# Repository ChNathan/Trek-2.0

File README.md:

# Trek-2.0
Project report and files for Oslo Met EPS project. We built a gait tracker for real time gait asymmetry over varying windows.

Included in this Repo Are:
- Trek EPS Report ( Which is covered in additional detail via this presentation https://docs.google.com/presentation/d/1eJzCRBbl3npr1pbE6kb9zn8NsA4ln3SlZraTO1EqVzs/edit?usp=sharing )
  - This report includes the project's purpose, progress, and future recommendations. We believe this project could be piloted in research studies with an additional project iteration.
- Firmware Code for Left and Right device, with and without SD Card
- User Interface Code
- Short user manual on setting up the device
- Autodesk Invetor CAD File for Case
- KiCad PCB Schematics, BOM, and additional design files

For any questions, comments, or concerns, please don't hestitate to contact us.
- Group 1, EPS Fall 2025

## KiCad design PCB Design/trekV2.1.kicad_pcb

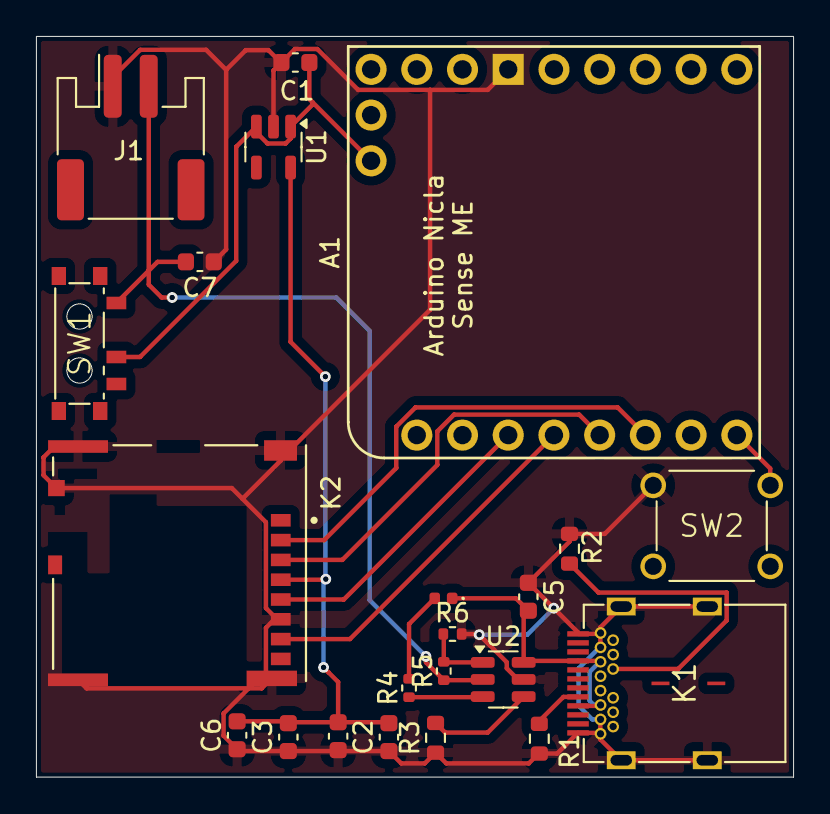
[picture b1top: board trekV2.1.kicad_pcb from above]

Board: 2 copper layers, 42.1 x 41.1 mm, 22 parts (0 on the bottom side), 16 nets.

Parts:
A1: Arduino_Nicla_Sense_ME_Socket; Arduino_Nicla_Voice_Socket
C1, C2, C5, C6: 2u2; C_0603_1608Metric
C3, C4: 100n; C_0603_1608Metric
C7: 4.7uF; C_0603_1608Metric
D1: red; LED_0402_1005Metric
J1: JST_02; JST_PH_S2B-PH-SM4-TB_1x02-1MP_P2.00mm_Horizontal
K1: 632723100011 USBC; CONN_WURTH_632723100011
K2: 503398-1892; MOLEX_503398-1892
R1, R2: 5k1; R_0603_1608Metric
R3: 1.33K; R_0603_1608Metric
R4: 2k2; R_0402_1005Metric
R5, R6: 10K; R_0402_1005Metric
SW1: Slide_Switch_SPDT_P3mm_10x5x10mm; SW_WURTH_450404015514
SW2: Push_Button; SW_KARSON_970-001-03-00
U1: SE5218; SOT-23-5
U2: BQ21040DBV; SOT-23-6

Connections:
3V3: C2.2, C3.2, C4.2, C6.2, K2.4 (VDD), U1.5 (VOUT)
CS_L: A1.D6 (D6_CS), K2.2 (CD/DAT3^2)
GND: A1.GND, C1.1, C2.1, C3.1, C4.1, C5.1, C6.1, C7.1, J1.1, K1.A1 (GND), K1.A12 (GND1), K1.B1 (GND2), K1.B12 (GND3), K1.GND, K1.GND1, K1.S1, K1.S2, K1.S3, K1.S4, K2.6 (VSS), K2.9 (VSS), K2.P1 (SHIELD), K2.P2 (SHIELD), K2.P3 (SHIELD), K2.P4 (SHIELD), R1.2, R2.2, R3.1, R6.2, SW2.2, U1.2 (GND), U2.5 (GND)
MISO_L: A1.D7 (D7_MISO), K2.7 (DAT0)
MOSI_L: A1.D8 (D8_MOSI), K2.3 (CMD)
unnamed: A1.D5, SW2.1
unnamed: D1.2 (K), R4.2
unnamed: K1.A5 (CC), R1.1
unnamed: K1.B5 (VCONN), R2.1
unnamed: R3.2, U2.4 (ISET)
unnamed: R5.2, R6.1, U2.1 (TS)
unnamed: R4.1, U2.3 (~CHG)
SCLK_L: A1.D9 (D9_SCK), K2.5 (CLK)
VBATRAW: C7.2, J1.2, R5.1, SW1.1, U2.2 (OUT)
VBATSYS: A1.VBAT, C1.2, SW1.2, U1.1 (VIN), U1.3 (EN)
VUSB: C5.2, D1.1 (A), K1.A4 (VBUS), K1.A9 (VBUS1), K1.B4 (VBUS2), K1.B9 (VBUS3), U2.6 (VIN)

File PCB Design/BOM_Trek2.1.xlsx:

Designators | Qty | Value | Description | Manufacturer | MPN | Package | Notes / DNP
U2 | 1.0 | BQ21040 | Li-ion 1-cell linear charger, SOT-23-6 | Texas Instruments | BQ21040DBVT | SOT-23-6 | TS mid-bias: R5/R6 10 k
U1 | 1.0 | 3.3 V, 600 mA | LDO Regulator, 3.3 V fixed, SOT-23-5 | SEASemi (or alt.) | SE5218-33 (alt: AP2112K-3.3) | SOT-23-5 | Input/Output caps 2.2 µF
K1 | 1.0 | USB-C Receptacle | 24-pin right-angle receptacle, mixed TH/SMD | Würth Elektronik | 6.32723100011E11 | Custom (mixed) | TH shell lugs to GND; hand-solder if no THT assembly
K2 | 1.0 | microSD Socket | Hinged microSD holder | Molex | 503398-1892 | Molex microSD | Place decouplers close
J1 | 1.0 | 2-pin, 2.0 mm | JST-PH battery header, side-entry, SMD | JST | BM02B-PH-SM4-TB(LF)(SN) | SMD | Battery connector
SW1 | 1.0 | SPDT | Slide switch, 3 mm pitch, ~10×5×10 mm | Generic / C&K | (e.g.) JS102011SAQN | TH | Battery isolate selector
SW2 | 1.0 | Momentary | THT pushbutton, 9.5 mm actuator | Karson | 970-001-03-00 | TH | Hand-solder if no THT assembly
D1 | 1.0 | Red LED | Red indicator LED | Any | 0402 red (e.g. LTST-C190KRKT) | 402.0 | Series R4 = 2.2 k to VUSB
R1, R2 | 2.0 | 5.1 k | USB-C CC pull-downs (to GND) | Any | 0.01 | 402.0 | For Sink-only
R3 | 1.0 | 1.33 k | BQ21040 ISET (charge current set) | Any | 0.01 | 402.0 | Sets I_CHG (~1 A per TI table)
R4 | 1.0 | 2.2 k | LED current-limit (D1) | Any | 0.01 | 402.0 | Red LED to VUSB
R5, R6 | 2.0 | 10 k | TS bias divider (midpoint ≈ VBAT/2) | Any | 0.01 | 402.0 | For thermistor bypass mode
C1 | 1.0 | 2.2 µF / 10 V | VIN (VUSB) input cap (charger) | Any | X5R/X7R | 603.0 | Close to U2 VIN
C7 | 1.0 | 4.7 µF / 6.3–10 V | VBAT output/rail cap (charger) | Any | X5R/X7R | 603.0 | Close to U2 OUT/VBAT
C2 | 1.0 | 2.2 µF / 10 V | LDO output (3V3) | Any | X5R/X7R | 603.0 | As per U1 datasheet
C5 | 1.0 | 2.2 µF / 10 V | LDO input (VCC/VBATSYS) | Any | X5R/X7R | 603.0 | As per U1 datasheet
C3, C4, C6 | 3.0 | 0.1 µF | Decouplers (microSD / local) | Any | X7R | 402.0 | Place close to K2 pins
FIDs (Top) | 3.0 | — | Global fiducials, 0.5 mm Cu, 1.5 mm mask | — | — | SMD pad | No paste; no net
A1 | 1.0 | Arduino Nicla | Castellated socket/footprint only | Arduino | Nicla Sense ME | Castellated | DNP (do not assemble)

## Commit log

2026-01-06 Initialize project folders with placeholders
2026-01-09 Jeya Codes
2026-01-09 Update README with project details and resources
    Added detailed project report and included links to resources.
2026-01-09 Thomas Codes
2026-01-14 Fix typo in README and add image
2026-01-14 Replace old image with a new one in README
